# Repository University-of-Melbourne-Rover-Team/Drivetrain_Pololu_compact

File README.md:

A smaller/compact version of the Pololu motor drive PCB board (BLFR)

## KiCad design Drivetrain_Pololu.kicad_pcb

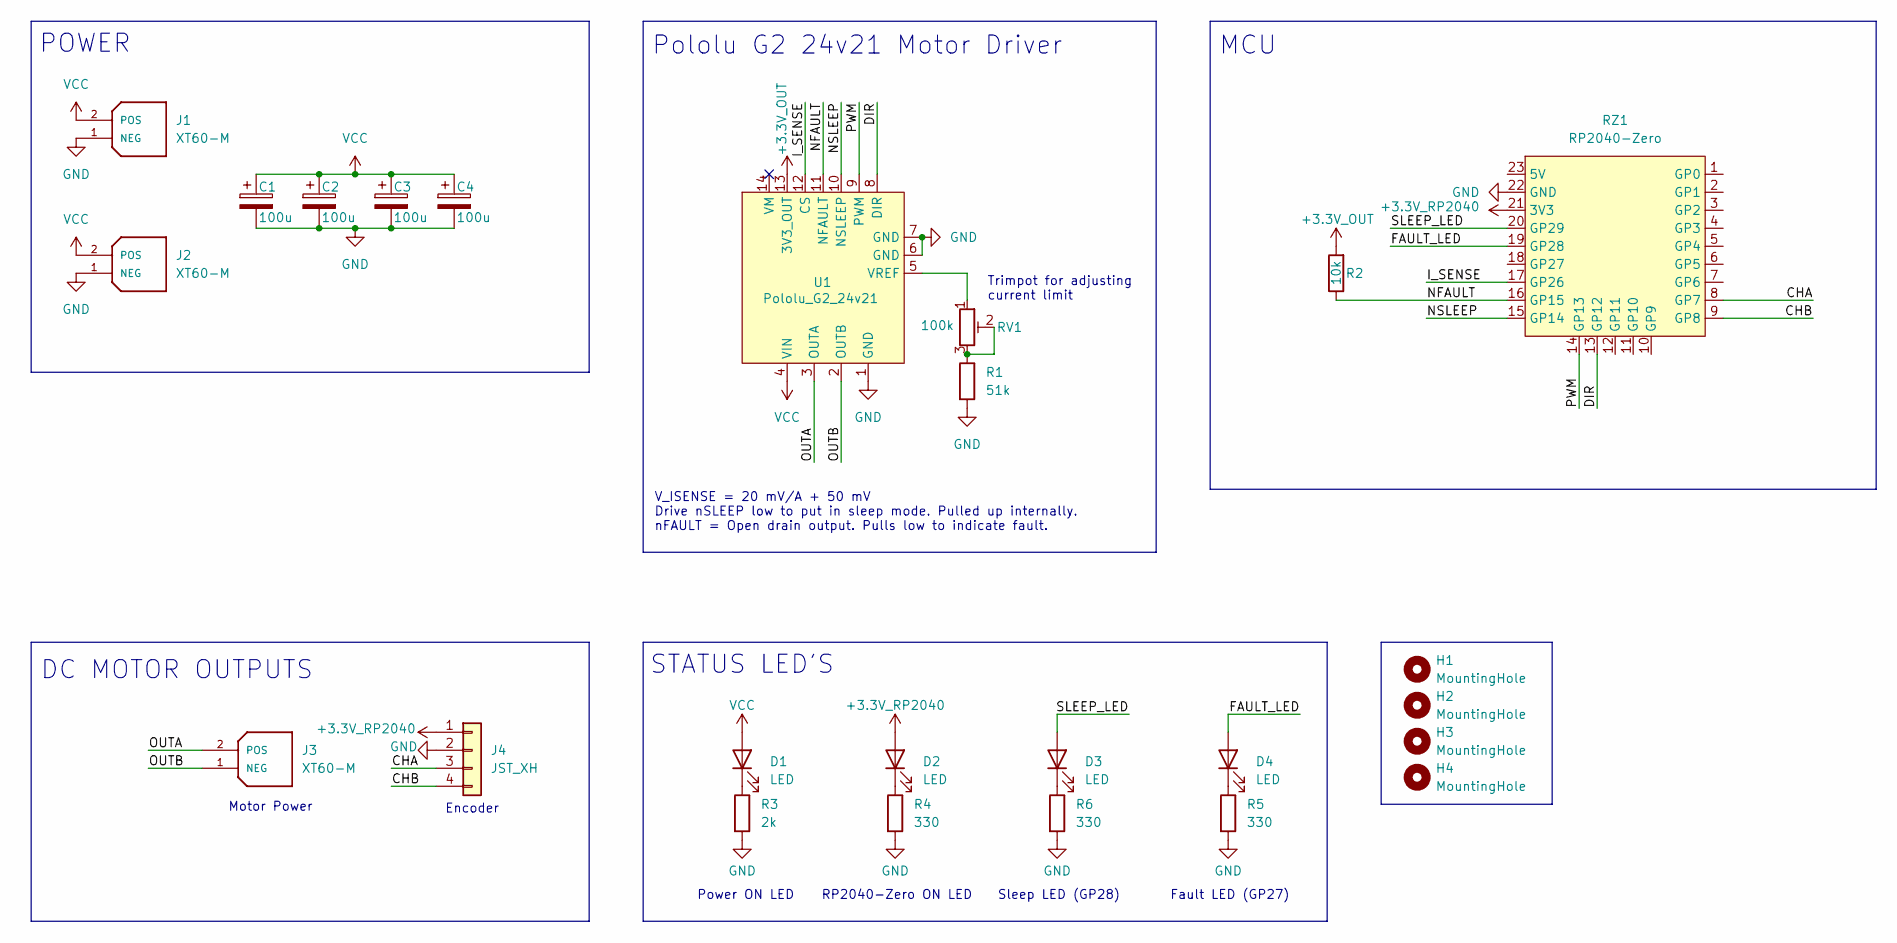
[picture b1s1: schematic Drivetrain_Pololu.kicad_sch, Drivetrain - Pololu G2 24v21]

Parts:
C1, C2, C3, C4: 100u; CP_Radial_D10.0mm_P2.50mm
D1, D2, D3, D4: LED; LED_0805_2012Metric_Pad1.15x1.40mm_HandSolder
H1, H2, H3, H4: MountingHole; MountingHole_3.2mm_M3_DIN965_Pad
J1, J2: XT60-M; AMASS_XT60PW-M_1x02_P7.20mm_Horizontal; PARTREV V1.2
J3: XT60-M; AMASS_XT60-M_1x02_P7.20mm_Vertical; PARTREV V1.2
J4: JST_XH; JST_XH_B4B-XH-A_1x04_P2.50mm_Vertical
R1: 51k; R_0805_2012Metric_Pad1.20x1.40mm_HandSolder
R2: 10k; R_0805_2012Metric_Pad1.20x1.40mm_HandSolder
R3: 2k; R_0805_2012Metric_Pad1.20x1.40mm_HandSolder
R4, R5, R6: 330; R_0805_2012Metric_Pad1.20x1.40mm_HandSolder
RV1: 100k; Potentiometer_Bourns_3296W_Vertical
RZ1: RP2040-Zero
U1: Pololu_G2_24v21

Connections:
+3.3V_OUT: R2.2, U1.13 (3V3_OUT)
+3.3V_RP2040: D2.2 (A), J4.1, RZ1.21 (3V3)
/CHA: J4.3, RZ1.8 (GP7)
/CHB: J4.4, RZ1.9 (GP8)
/DIR: RZ1.13 (GP12), U1.8 (DIR)
/FAULT_LED: D4.2 (A), RZ1.19 (GP28)
/I_SENSE: RZ1.17 (GP26), U1.12 (CS)
/NFAULT: R2.1, RZ1.16 (GP15), U1.11 (NFAULT)
/NSLEEP: RZ1.15 (GP14), U1.10 (NSLEEP)
/OUTA: J3.2 (POS), U1.3 (OUTA)
/OUTB: J3.1 (NEG), U1.2 (OUTB)
/PWM: RZ1.14 (GP13), U1.9 (PWM)
/SLEEP_LED: D3.2 (A), RZ1.20 (GP29)
GND: C1.2, C2.2, C3.2, C4.2, J1.1 (NEG), J2.1 (NEG), J4.2, R1.2, R3.2, R4.2, R5.2, R6.2, RZ1.22 (GND), U1.1 (GND), U1.6 (GND), U1.7 (GND)
unnamed: D1.1 (K), R3.1
unnamed: D2.1 (K), R4.1
unnamed: D3.1 (K), R6.1
unnamed: D4.1 (K), R5.1
unnamed: R1.1, RV1.2, RV1.3
unnamed: RV1.1, U1.5 (VREF)
VCC: C1.1, C2.1, C3.1, C4.1, D1.2 (A), J1.2 (POS), J2.2 (POS), U1.4 (VIN)

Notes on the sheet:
Trimpot for adjusting current limit
STATUS LED'S
Fault LED (GP27)
MCU
Pololu G2 24v21 Motor Driver
Motor Power
RP2040-Zero ON LED
V_ISENSE = 20 mV/A + 50 mV Drive nSLEEP low to put in sleep mode. Pulled up internally. nFAULT = Open drain output. Pulls low to indicate fault.
POWER
Power ON LED
Encoder
DC MOTOR OUTPUTS
Sleep LED (GP28)

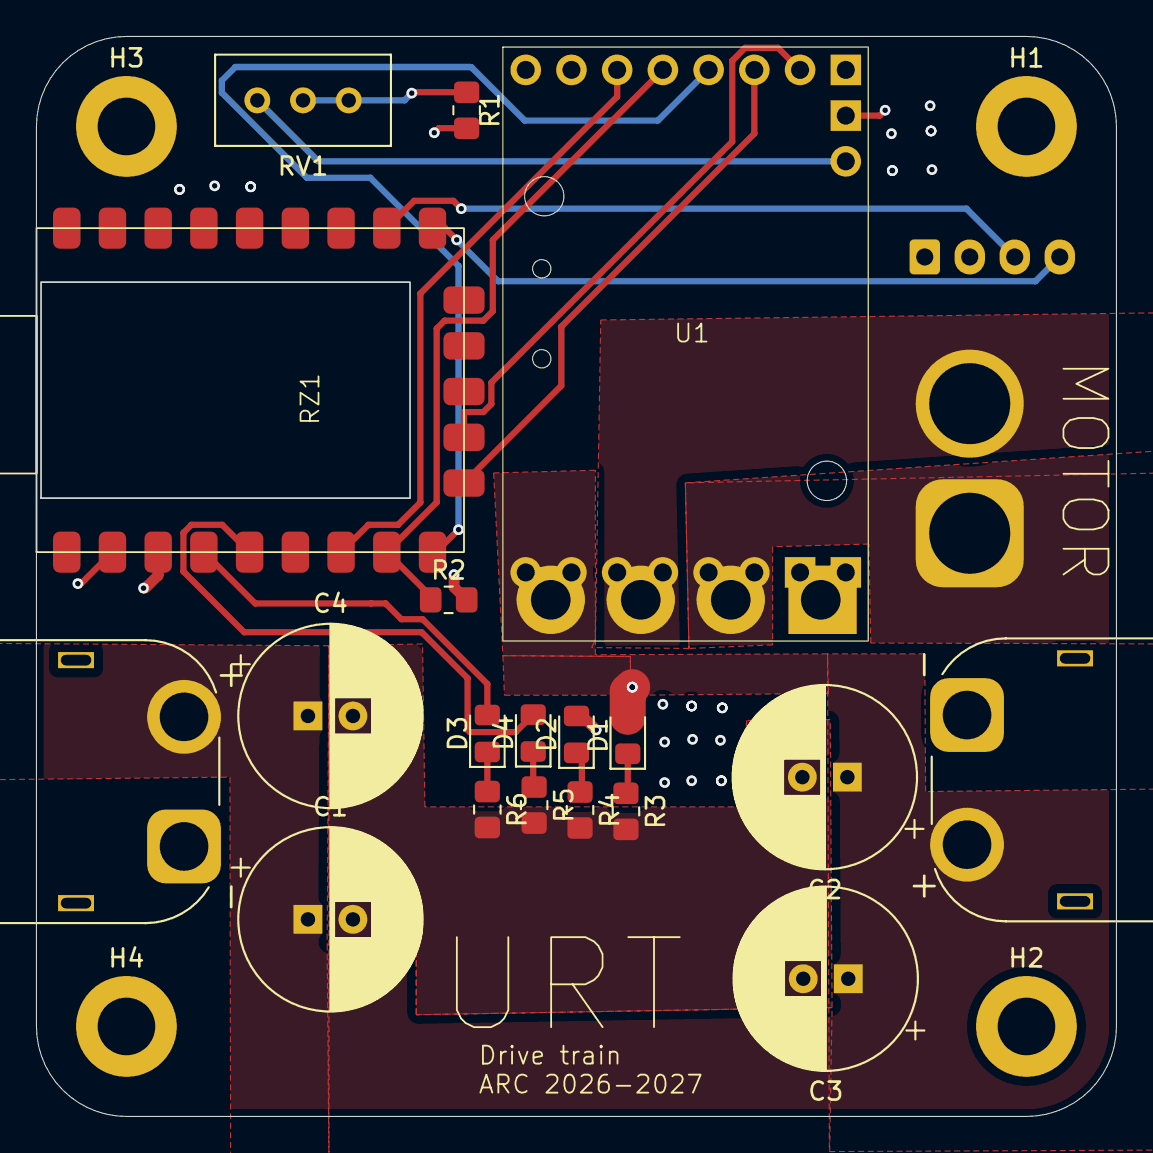
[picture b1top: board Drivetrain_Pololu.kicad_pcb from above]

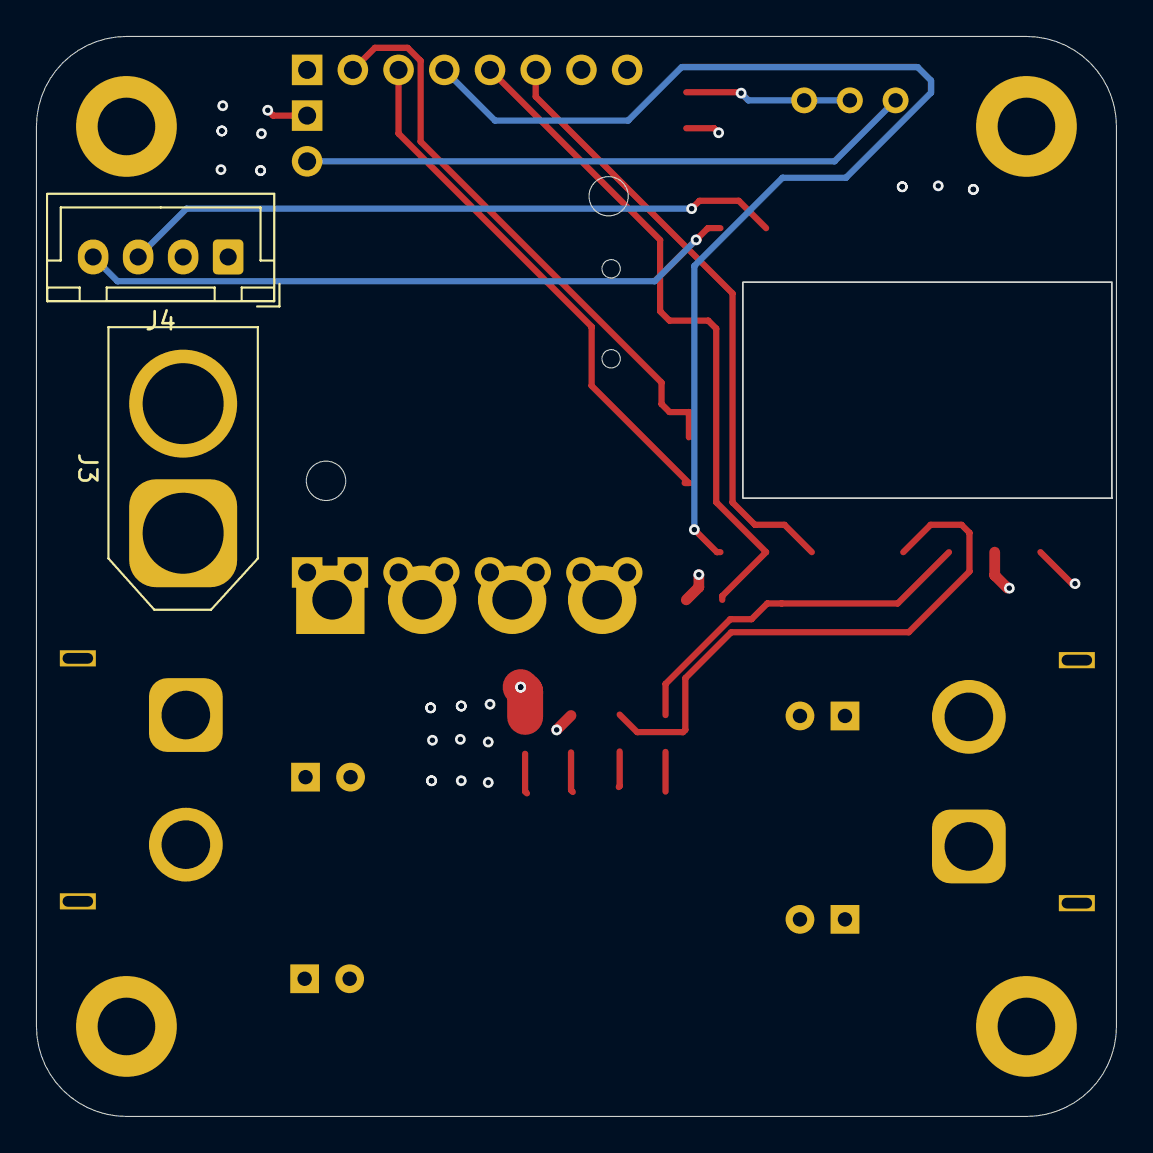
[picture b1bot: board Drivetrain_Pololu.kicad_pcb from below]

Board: 4 copper layers, 60.0 x 60.0 mm, 25 parts (2 on the bottom side), 21 nets.
